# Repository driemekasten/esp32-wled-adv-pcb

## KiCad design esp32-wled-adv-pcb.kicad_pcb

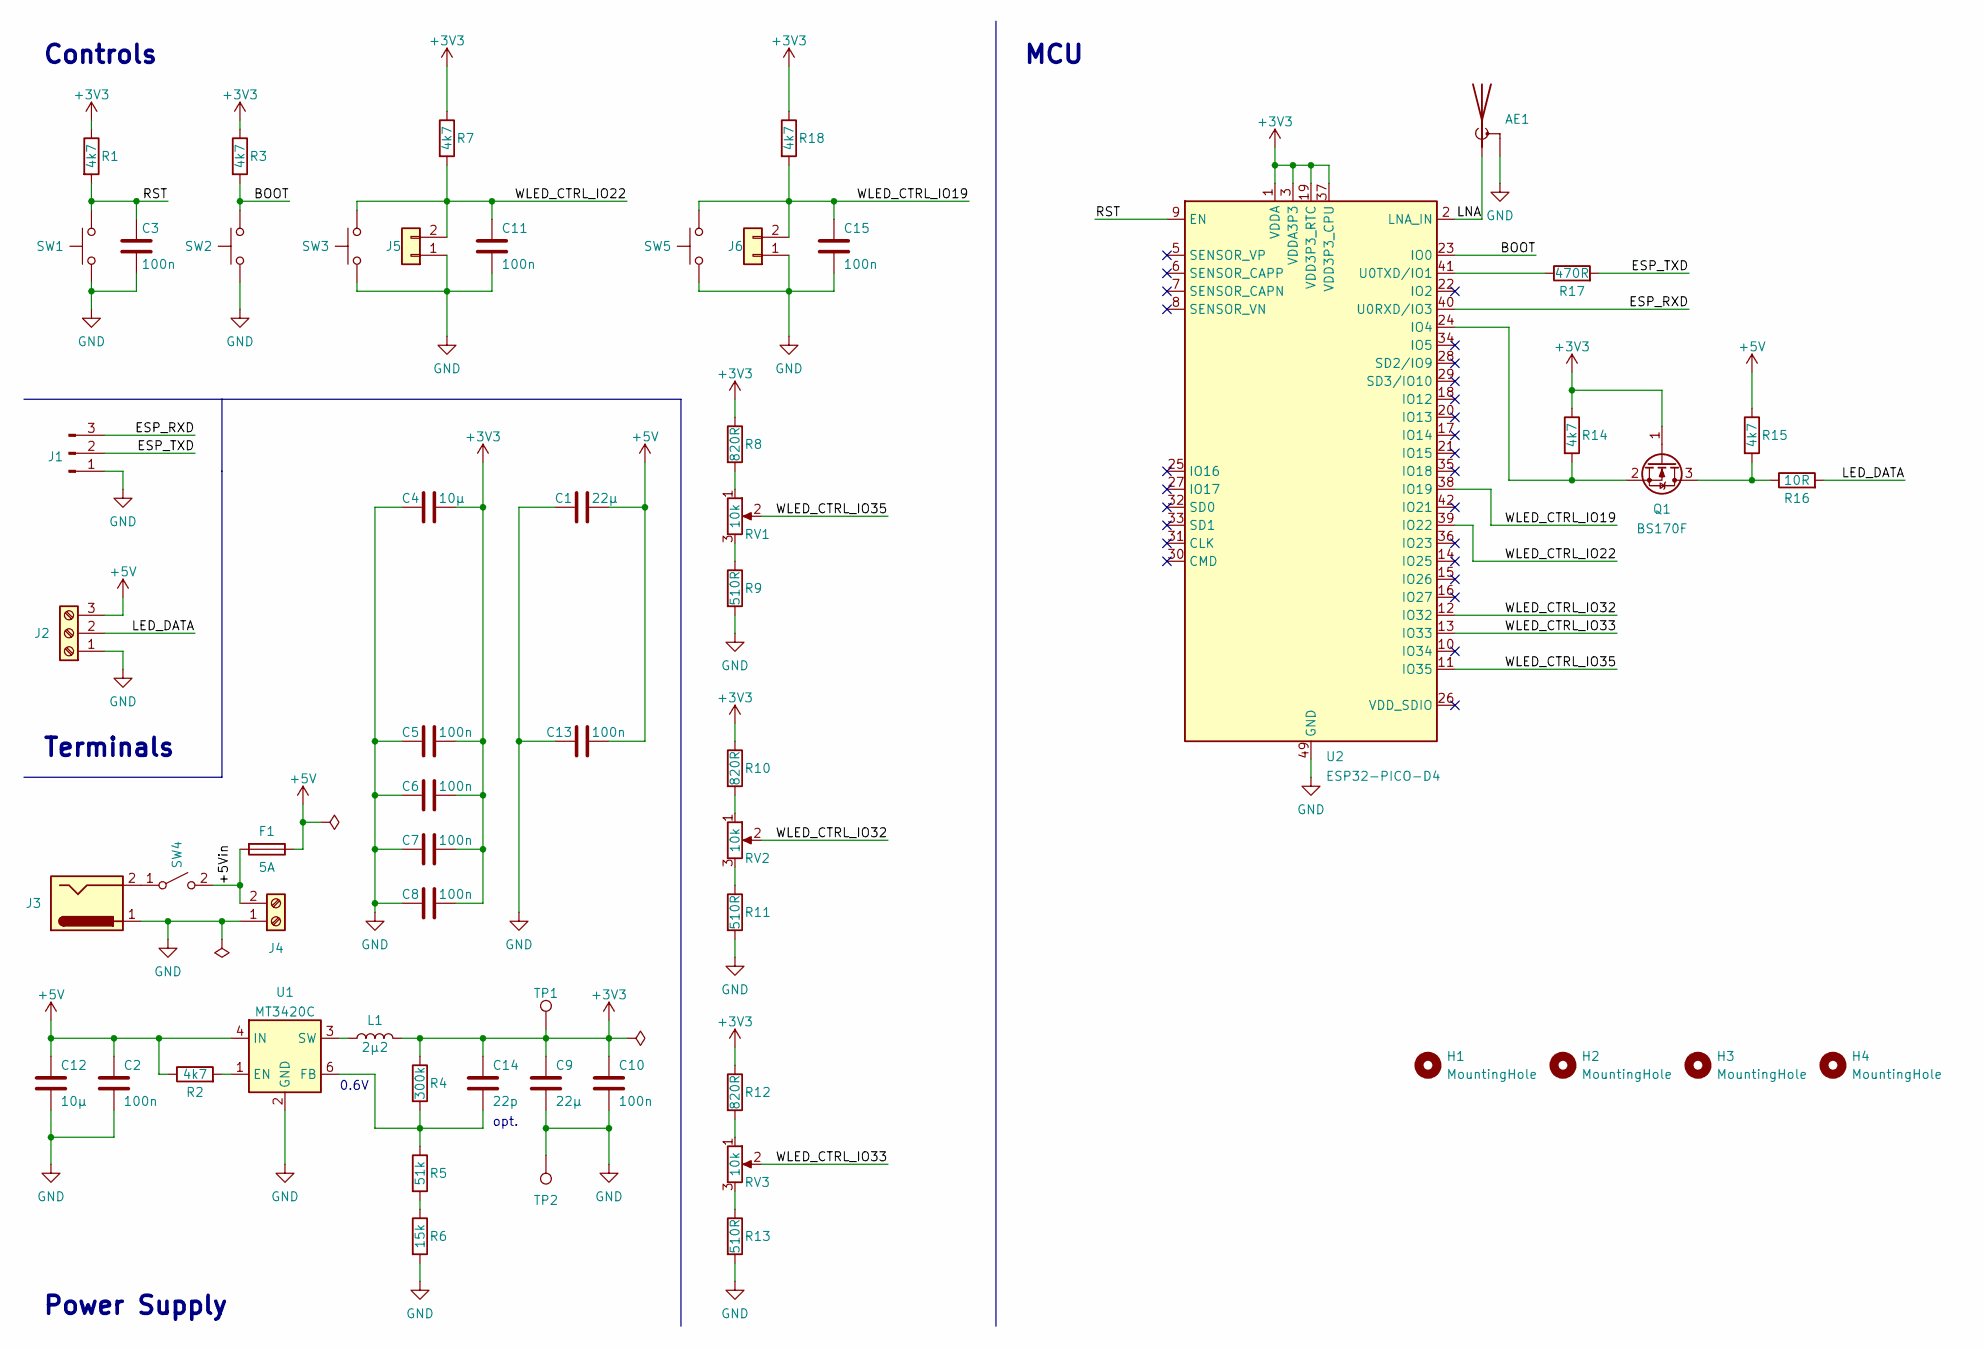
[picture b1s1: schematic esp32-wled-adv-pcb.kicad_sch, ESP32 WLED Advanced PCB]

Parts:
AE1: Antenna_Shield; Texas_SWRA117D_2.4GHz_Right
C1, C9: 22µ; C_0805_2012Metric
C2, C3, C5, C6, C7, C8, C10, C11, C13, C15: 100n; C_0805_2012Metric
C4, C12: 10µ; C_0805_2012Metric
C14: 22p; C_0805_2012Metric
F1: 5A; Fuseholder_Cylinder-5x20mm_Stelvio-Kontek_PTF78_Horizontal_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
H1, H2, H3, H4: MountingHole; MountingHole_3.2mm_M3_DIN965
J1: Conn_01x03_Male; PinHeader_1x03_P2.54mm_Vertical
J2: Conn_01x03_Male; KF103-5.0-3P
J3: Barrel_Jack; BarrelJack_Horizontal
J4: Screw_Terminal_01x02; KF103-5.0-2P
J5, J6: Conn_01x02; PinHeader_1x02_P2.54mm_Vertical
L1: 2µ2; Sumida 252012CDMCD_DS; Part 252012DMCD/DS
Q1: BS170F; SOT-23
R1, R2, R3, R7, R14, R15, R18: 4k7; R_0805_2012Metric
R4: 300k; R_0805_2012Metric
R5: 51k; R_0805_2012Metric
R6: 15k; R_0805_2012Metric
R8, R10, R12: 820R; R_0805_2012Metric
R9, R11, R13: 510R; R_0805_2012Metric
R16: 10R; R_0805_2012Metric
R17: 470R; R_0805_2012Metric
RV1, RV2, RV3: 10k; Potentiometer_Bourns_PDB181-K415K-x
SW1, SW2: SW_Push; SW_XUNPU_TS-1077S
SW3, SW5: SW_Push
SW4: SW_SPST
TP1: 3V3; TestPoint_THTPad_D1.0mm_Drill0.5mm
TP2: GND; TestPoint_THTPad_D1.0mm_Drill0.5mm
U1: MT3420C; SOT-23-6
U2: ESP32-PICO-D4; QFN-48-1EP_7x7mm_P0.5mm_EP5.3x5.3mm

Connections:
+3V3: C4.2, C5.2, C6.2, C7.2, C8.2, C9.1, C10.1, C14.1, L1.2, Q1.1 (G), R1.1, R3.1, R4.1, R7.1, R8.1, R10.1, R12.1, R14.1, R18.1, TP1.1, U2.1 (VDDA), U2.3 (VDDA3P3), U2.4 (VDDA3P3), U2.19 (VDD3P3_RTC), U2.37 (VDD3P3_CPU), U2.43 (VDDA), U2.46 (VDDA)
+5V: C1.2, C2.1, C12.1, C13.2, F1.1, J2.3, R2.1, R15.1, U1.4 (IN)
/+5Vin: F1.2, J4.2, SW4.2 (B)
/BOOT: R3.2, SW2.2, U2.23 (IO0)
/ESP_RXD: J1.3, U2.40 (U0RXD/IO3)
/ESP_TXD: J1.2, R17.2
/LED_DATA: J2.2, R16.2
/LNA: AE1.1 (A), U2.2 (LNA_IN)
/RST: C3.2, R1.2, SW1.2, U2.9 (EN)
/WLED_CTRL_IO19: C15.1, J6.2, R18.2, SW5.2, U2.38 (IO19)
/WLED_CTRL_IO22: C11.1, J5.2, R7.2, SW3.2, U2.39 (IO22)
/WLED_CTRL_IO32: RV2.2, U2.12 (IO32)
/WLED_CTRL_IO33: RV3.2, U2.13 (IO33)
/WLED_CTRL_IO35: RV1.2, U2.11 (IO35)
GND: AE1.2 (Shield), C1.1, C2.2, C3.1, C4.1, C5.1, C6.1, C7.1, C8.1, C9.2, C10.2, C11.2, C12.2, C13.1, C15.2, J1.1, J2.1, J3.1, J4.1, J5.1, J6.1, R6.2, R9.2, R11.2, R13.2, SW1.1, SW2.1, SW3.1, SW5.1, TP2.1, U1.2 (GND), U2.49 (GND)
unnamed: C14.2, R4.2, R5.1, U1.6 (FB)
unnamed: J3.2, SW4.1 (A)
unnamed: L1.1, U1.3 (SW)
unnamed: Q1.2 (S), R14.2, U2.24 (IO4)
unnamed: Q1.3 (D), R15.2, R16.1
unnamed: R2.2, U1.1 (EN)
unnamed: R5.2, R6.1
unnamed: R8.2, RV1.1
unnamed: R9.1, RV1.3
unnamed: R10.2, RV2.1
unnamed: R11.1, RV2.3
unnamed: R12.2, RV3.1
unnamed: R13.1, RV3.3
unnamed: R17.1, U2.41 (U0TXD/IO1)

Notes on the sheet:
0.6V
Terminals
Controls
opt.
Power Supply
MCU

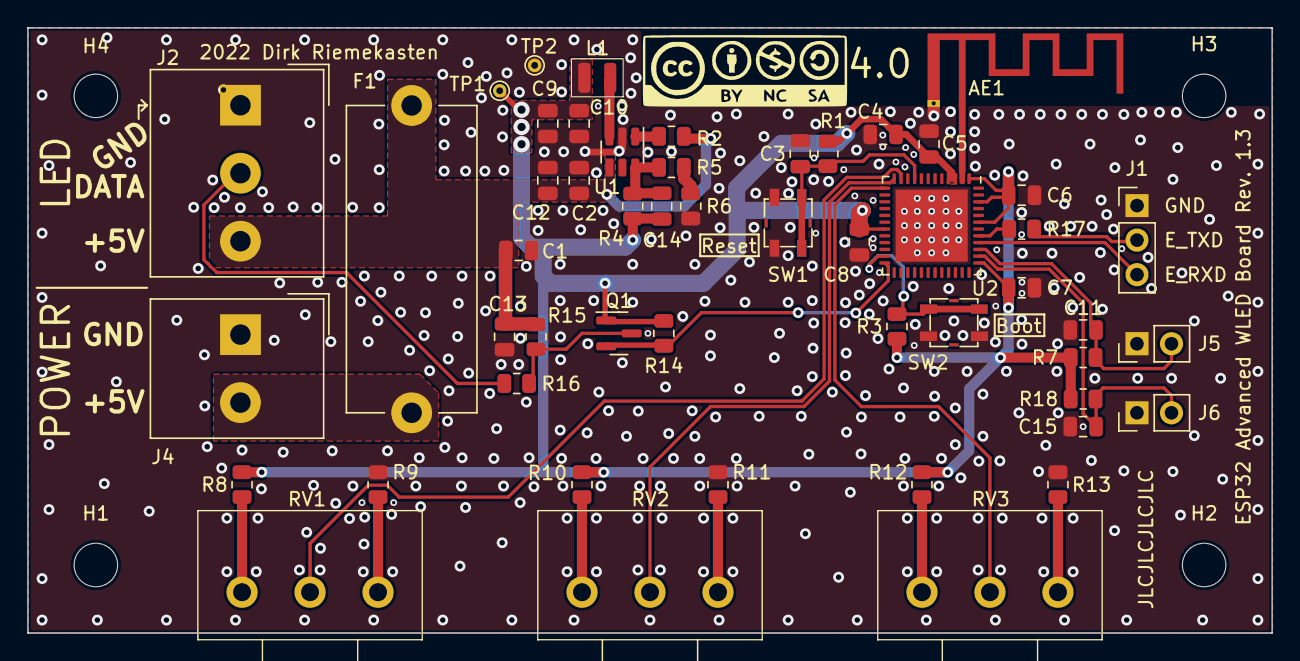
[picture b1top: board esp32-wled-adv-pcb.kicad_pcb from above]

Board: 2 copper layers, 91.5 x 44.5 mm, 55 parts (0 on the bottom side), 28 nets.

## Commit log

2022-01-29 commit empty project
2022-01-31 commit intermediate work
2022-01-31 add backup-folder to .gitignore and delete backup-folder
2022-01-31 finalize first version of schematic
2022-01-31 assign footprints, refresh pdf of schematic
2022-02-04 finalize Rev 1
2022-02-04 correct scaled potentiometer step file
2022-02-05 add missing silkscreen text for boot and reset switch, refresh schematic and images
2022-02-05 add interactive html bom
2022-02-07 set pcb origin
2022-02-22 change series resistor values for potentiometers
2022-02-23 change GPIOs for analog inputs and add a second pushbutton
